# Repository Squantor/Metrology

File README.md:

# General Metrology related projects/tools
This repository contains metrology related hardware/software/mechcanical parts. Stuff like tools, jigs, adapters etc.
## Structure
* [electronics](electronics/README.md) contains all the electronic hardware used in the project.
* [software](software/README.md) contains all the software used in the project. This can be embedded, PC/smartphone or test scripts, anything a computer can execute resides here.
* [mechanical](mechanical/README.md) contains all the CAD drawings, mostly 3d printable objects.
* [documentation](documentation/index.md) contains all project documentation, logs, research, papers, datasheets and more.
## Cloning
This repository makes extensive use of submodules, use ```git clone --recurse-submodules https://github.com/Squantor/Metrology.git``` to clone everything in one go.

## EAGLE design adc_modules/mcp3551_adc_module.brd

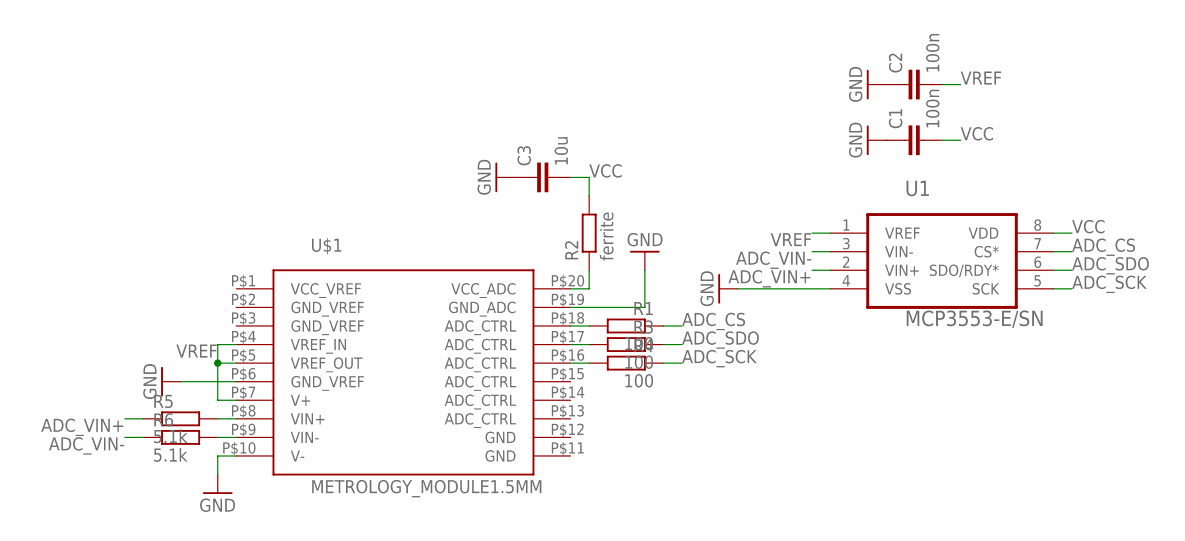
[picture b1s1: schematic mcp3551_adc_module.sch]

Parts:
C1, C2: 100n; C0603
C3: 10u; C0805
R1, R3, R4: 100; R0603
R2: ferrite; R0805
R5, R6: 5.1k; R0805
U1: MCP3553-E/SN; SOIC127P600X175-8N
U$1: METROLOGY_MODULE1.5MM; METROLOGY_MODULE_1.5MM_HOLE

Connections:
ADC_CS: R1.1, U1.7 (CS*)
ADC_SCK: R4.1, U1.5 (SCK)
ADC_SDO: R3.1, U1.6 (SDO/RDY*)
ADC_VIN+: R5.1, U1.2 (VIN+)
ADC_VIN-: R6.1, U1.3 (VIN-)
GND: C1.1, C2.1, C3.1, U1.4 (VSS), U$1.P$6 (GND_VREF), U$1.P$10 (V-), U$1.P$19 (GND_ADC)
unnamed: R2.1, U$1.P$20 (VCC_ADC)
unnamed: R1.2, U$1.P$18 (ADC_CTRL)
unnamed: R3.2, U$1.P$17 (ADC_CTRL)
unnamed: R4.2, U$1.P$16 (ADC_CTRL)
unnamed: R5.2, U$1.P$8 (VIN+)
unnamed: R6.2, U$1.P$9 (VIN-)
VCC: C1.2, C3.2, R2.2, U1.8 (VDD)
VREF: C2.2, U1.1 (VREF), U$1.P$4 (VREF_IN), U$1.P$5 (VREF_OUT), U$1.P$7 (V+)

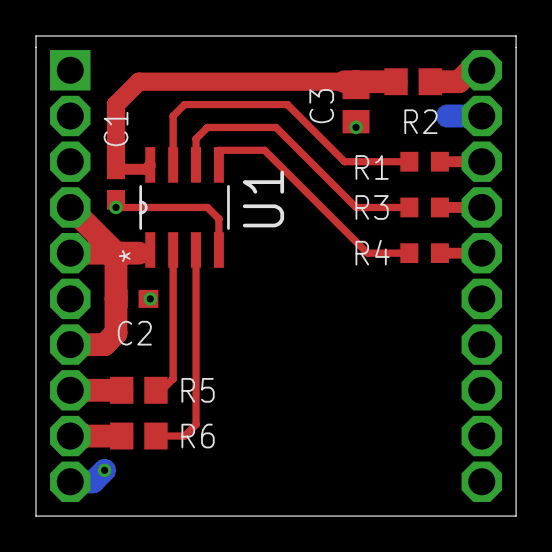
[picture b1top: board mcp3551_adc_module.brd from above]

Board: 2 copper layers, 26.7 x 26.7 mm, 11 parts (0 on the bottom side), 14 nets.

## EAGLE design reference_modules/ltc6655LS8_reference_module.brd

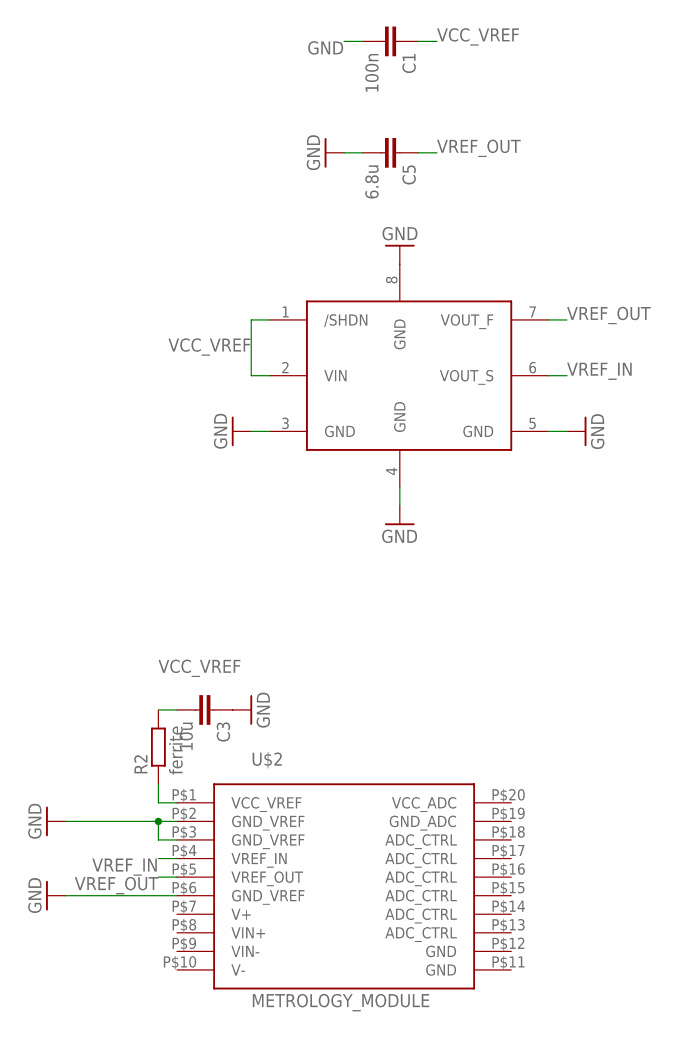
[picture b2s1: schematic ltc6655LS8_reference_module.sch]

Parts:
C1: 100n; C0603
C3: 10u; C0805
C5: 6.8u; C050-075X075
R2: ferrite; R0805
U$1: LTC6655LS8_ELONG; LS8_ELONG
U$2: METROLOGY_MODULE

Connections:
GND: C1.2, C3.1, C5.2, U$1.3 (GND), U$1.4 (GND), U$1.5 (GND), U$1.8 (GND), U$2.P$2 (GND_VREF), U$2.P$3 (GND_VREF), U$2.P$6 (GND_VREF)
unnamed: R2.1, U$2.P$1 (VCC_VREF)
VCC_VREF: C1.1, C3.2, R2.2, U$1.1 (/SHDN), U$1.2 (VIN)
VREF_IN: U$1.6 (VOUT_S), U$2.P$4 (VREF_IN)
VREF_OUT: C5.1, U$1.7 (VOUT_F), U$2.P$5 (VREF_OUT)

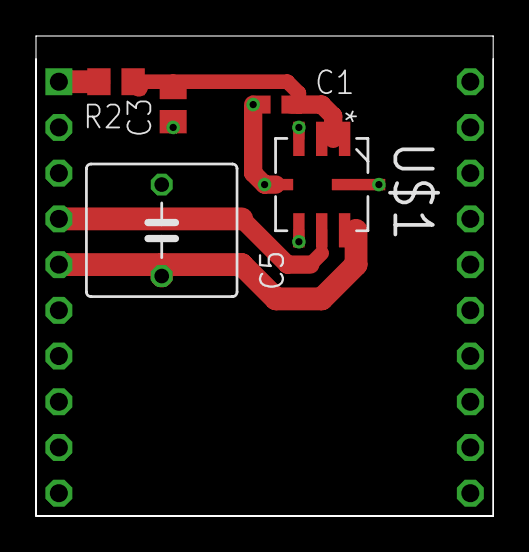
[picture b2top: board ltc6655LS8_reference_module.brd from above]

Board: 2 copper layers, 25.4 x 26.7 mm, 6 parts (0 on the bottom side), 5 nets.

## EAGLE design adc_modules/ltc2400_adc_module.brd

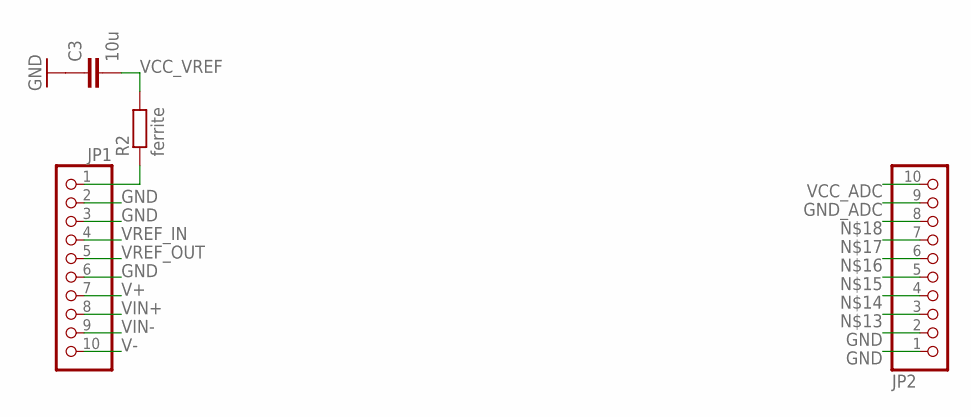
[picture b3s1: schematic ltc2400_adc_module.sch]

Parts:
C3: 10u; C0805
JP1, JP2: PINHD-1X10NORM_OCT; 1X10_NORMAL_OCT
R2: ferrite; R0805

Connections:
GND: C3.1, JP1.2, JP1.3, JP1.6, JP2.1, JP2.2
GND_ADC: JP2.9
unnamed: JP1.1, R2.1
V+: JP1.7
V-: JP1.10
VCC_ADC: JP2.10
VCC_VREF: C3.2, R2.2
VIN+: JP1.8
VIN-: JP1.9
VREF_IN: JP1.4
VREF_OUT: JP1.5

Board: 2 copper layers, 4 parts (0 on the bottom side), 3 nets, no tracks yet.

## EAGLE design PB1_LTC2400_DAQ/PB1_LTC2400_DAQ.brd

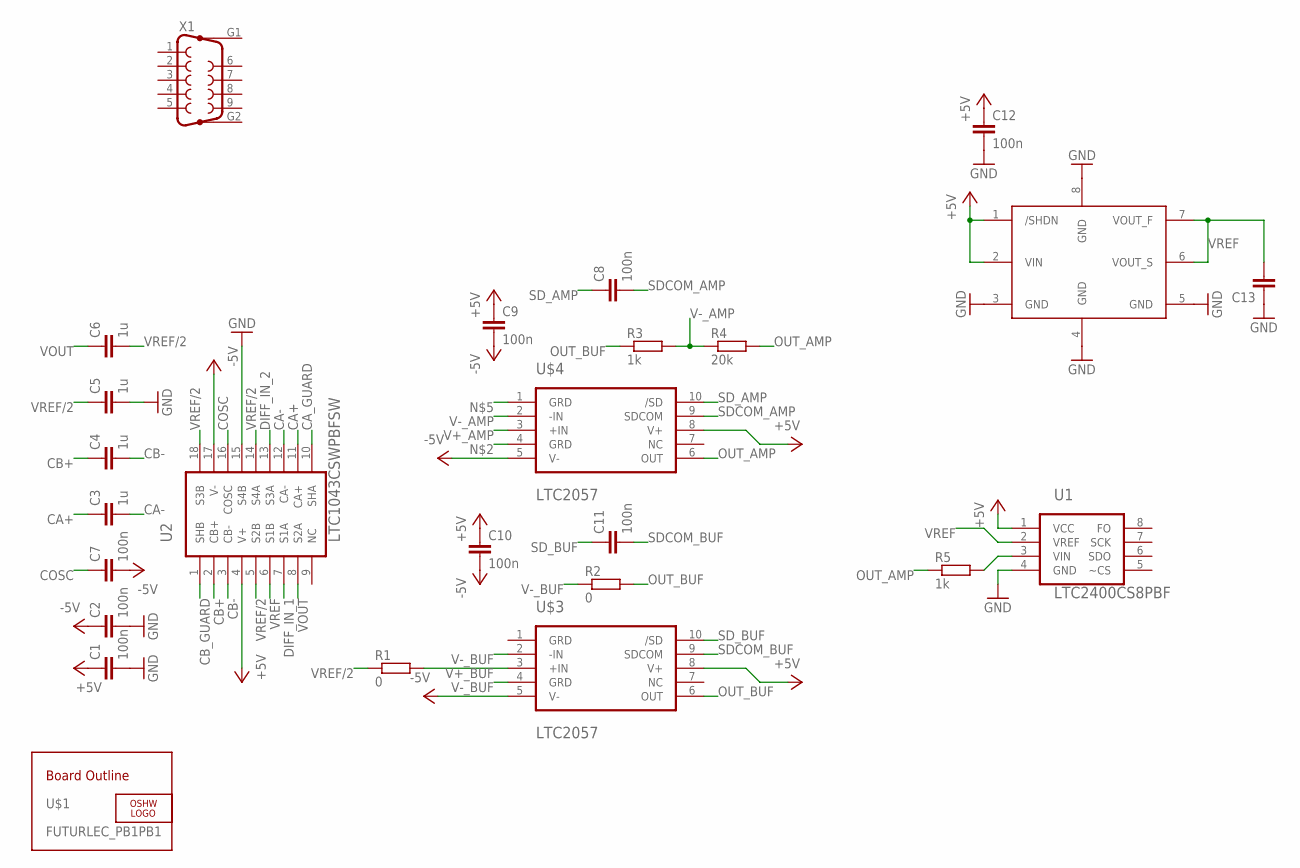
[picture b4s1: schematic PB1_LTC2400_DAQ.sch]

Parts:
C1, C2, C7, C9, C10, C12: 100n; C1812K
C3, C4, C5, C6: 1u; C2220K
C8, C11: 100n; C0603
C13: C-EU075-063X106; C075-063X106
LOGO1: OSHW_LOGO_8MILX0200-NT; OSHW_8X200_NOTEXT
R1, R2: 0; R0805
R3, R5: 1k; R0805
R4: 20k; R0805
U1: LTC2400CS8PBF; SOIC127P600X175-8N
U2: LTC1043CSWPBFSW; SOIC127P1032X264-18N
U$1: FUTURLEC_PB1PB1; FUTURLEC_PB1
U$2: LTC6655LS8_ELONG; LS8_ELONG
U$3, U$4: LTC2057; MS-MSOP10
X1: F09VP

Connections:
+5V: C1.1, C9.1, C10.1, C12.1, U1.1 (VCC), U2.4 (V+), U$2.1 (/SHDN), U$2.2 (VIN), U$3.8 (V+), U$4.8 (V+)
-5V: C2.1, C7.2, C9.2, C10.2, U2.17 (V-), U$3.5 (V-), U$4.5 (V-)
CA+: C3.1, U2.11 (CA+)
CA-: C3.2, U2.12 (CA-)
CA_GUARD: U2.10 (SHA)
CB+: C4.1, U2.2 (CB+)
CB-: C4.2, U2.3 (CB-)
CB_GUARD: U2.1 (SHB)
COSC: C7.1, U2.16 (COSC)
DIFF_IN_1: U2.7 (S1A)
DIFF_IN_2: U2.13 (S3A)
GND: C1.2, C2.2, C5.2, C12.2, C13.1, U1.4 (GND), U2.15 (S4B), U$2.3 (GND), U$2.4 (GND), U$2.5 (GND), U$2.8 (GND)
unnamed: R5.2, U1.3 (VIN)
OUT_AMP: R4.2, R5.1, U$4.6 (OUT)
OUT_BUF: R2.2, R3.1, U$3.6 (OUT)
SDCOM_AMP: C8.2, U$4.9 (SDCOM)
SDCOM_BUF: C11.2, U$3.9 (SDCOM)
SD_AMP: C8.1, U$4.10 (/SD)
SD_BUF: C11.1, U$3.10 (/SD)
V+_AMP: U$4.3 (+IN)
V+_BUF: R1.2, U$3.3 (+IN)
V-_AMP: R3.2, R4.1, U$4.2 (-IN)
V-_BUF: R2.1, U$3.2 (-IN), U$3.4 (GRD)
VOUT: C6.1, U2.8 (S2A)
VREF: C13.2, U1.2 (VREF), U2.6 (S1B), U$2.6 (VOUT_S), U$2.7 (VOUT_F)
VREF/2: C5.1, C6.2, R1.1, U2.5 (S2B), U2.14 (S4A), U2.18 (S3B)

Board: 2 copper layers, 26 parts (2 on the bottom side), 21 nets, no tracks yet.

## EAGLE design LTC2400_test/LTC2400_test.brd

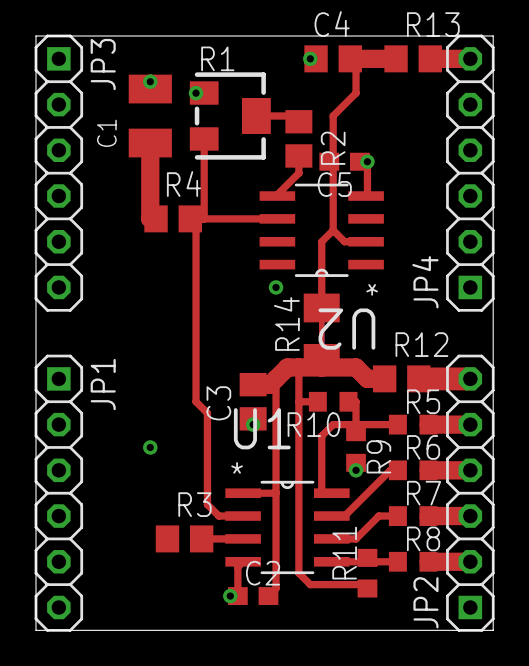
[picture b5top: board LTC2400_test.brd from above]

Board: 2 copper layers, 25.4 x 33.0 mm, 26 parts (1 on the bottom side), 17 nets.

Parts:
C1: SMC_B
C2, C5: 100n; C0603
C3, C4: 10u; C0805
JP1, JP2, JP3, JP4: 1X06_SMALL
R1: 100k; RTRIM3214W
R2: 4.7M; R0805
R3: 5.1k; R0805
R4: 2.2; R0805
R5, R6, R7, R8: 100; R0603
R9: 60Hz; R0603
R10: 50Hz; R0603
R11: 10k; R0603
R12, R13: ferrite; R0805
R14, R15: M1206
U1: LTC2400CS8PBF; SOIC127P600X175-8N@1
U2: LT1019A-2.5PBFS8; SOIC127P600X175-8N

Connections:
+5V: C2.2, C3.2, C4.2, C5.2, R10.2, R11.1, R12.1, R13.1, R14.1, R14.2, U1.1, U2.2
CS: R8.1, R11.2, U1.5
FO: R5.1, R9.1, R10.1, U1.8
GND: C1.-, C2.1, C3.1, C4.1, C5.1, JP1.2, JP1.4, JP1.6, JP2.1, JP3.6, JP4.1, R1.1, R9.2, R15.1, R15.2, U1.4, U2.4
unnamed: JP4.6, R13.2
unnamed: JP2.6, R12.2
unnamed: C1.+, R4.1
unnamed: R3.2, U1.3
unnamed: R1.2, R2.1
unnamed: JP2.2, R8.2
unnamed: JP2.3, R7.2
unnamed: JP2.4, R6.2
unnamed: JP2.5, R5.2
SCK: R6.1, U1.7
SDO: R7.1, U1.6
TRIM: R2.2, U2.5
VREF: R1.3, R4.2, U1.2, U2.6

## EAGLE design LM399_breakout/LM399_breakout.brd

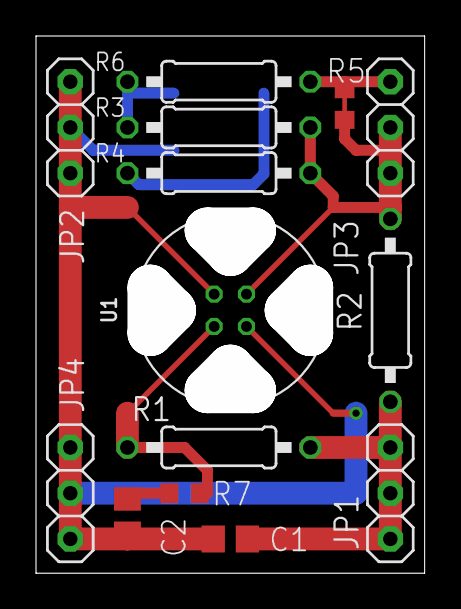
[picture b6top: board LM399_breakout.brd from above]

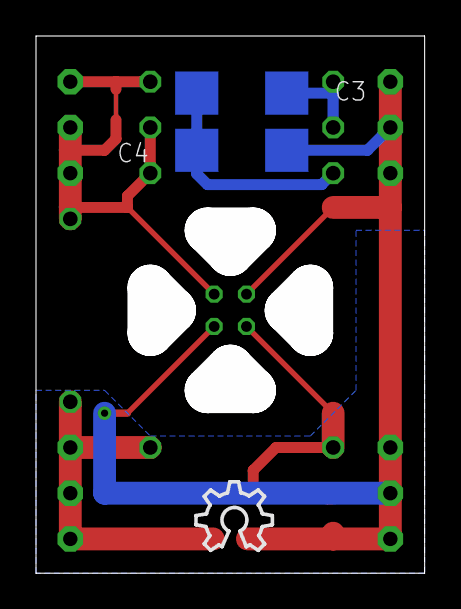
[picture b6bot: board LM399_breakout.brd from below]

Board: 2 copper layers, 21.6 x 29.8 mm, 17 parts (3 on the bottom side), 7 nets.

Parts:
C1: 1u; C0805
C2: 10u; C0805
C3, C4: SMC_C
JP1: VCC; 1X03_SMALL
JP2, JP4: GND; 1X03_SMALL
JP3: Zener; 1X03_SMALL
R1: inrush; 0207/10
R2: 220k; 0207/10
R3, R4, R6: 0207/10
R5: WIRE0603; R0603/BRIDGE
R7: R0603
U1: LM399; H4-TO46-4PIN
U$1: OSHW_8X150_NOTEXT

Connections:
+15V: C1.1, JP1.1, JP1.2, JP1.3, R1.2, R2.2
GND: C1.2, C2.2, C4.-, JP2.1, JP2.2, JP2.3, JP4.1, JP4.2, JP4.3, U1.2, U1.4
unnamed: R1.1, R7.1, U1.3
unnamed: C2.1, R7.2
unnamed: C3.-, C4.+, R4.2
unnamed: C3.+, R3.2, R6.1
ZENER: JP3.1, JP3.2, JP3.3, R2.1, R3.1, R4.1, R5.1, R5.2, R6.2, U1.1

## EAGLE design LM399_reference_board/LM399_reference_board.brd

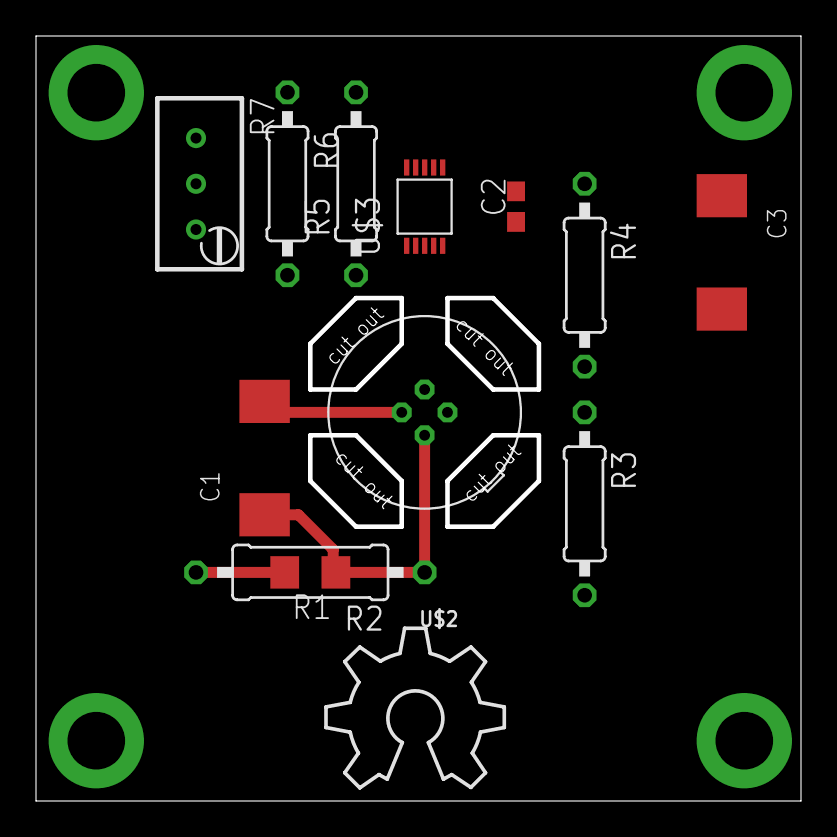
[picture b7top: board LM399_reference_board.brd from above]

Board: 2 copper layers, 42.5 x 42.5 mm, 13 parts (0 on the bottom side), 7 nets.

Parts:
C1, C3: 10u; SMC_D
C2: 100n; C0603
R1: inrush; R1206
R2: inrush; 0309/12
R3: 220k; 0207/10
R4: 5k; 0207/10
R5: 8.8k; 0207/10
R6: 19k; 0207/10
R7: RTRIMT93YA
U$1: OSHW_8X350_NOTEXT
U$2: LM399; H4-TO46-4PIN
U$3: LTC2057; MS-MSOP10

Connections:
+15V: C2.2, C3.+, R1.2, R2.2, R3.2, U$3.8
GND: C1.-, C2.1, C3.-, R7.2, R7.3, U$2.2, U$2.3, U$3.5
unnamed: C1.+, R1.1, R2.1, U$2.4
unnamed: R5.1, R6.2, U$3.1, U$3.2, U$3.4
unnamed: R4.1, R5.2, U$3.6
unnamed: R6.1, R7.1
VZENER: R3.1, R4.2, U$2.1, U$3.3

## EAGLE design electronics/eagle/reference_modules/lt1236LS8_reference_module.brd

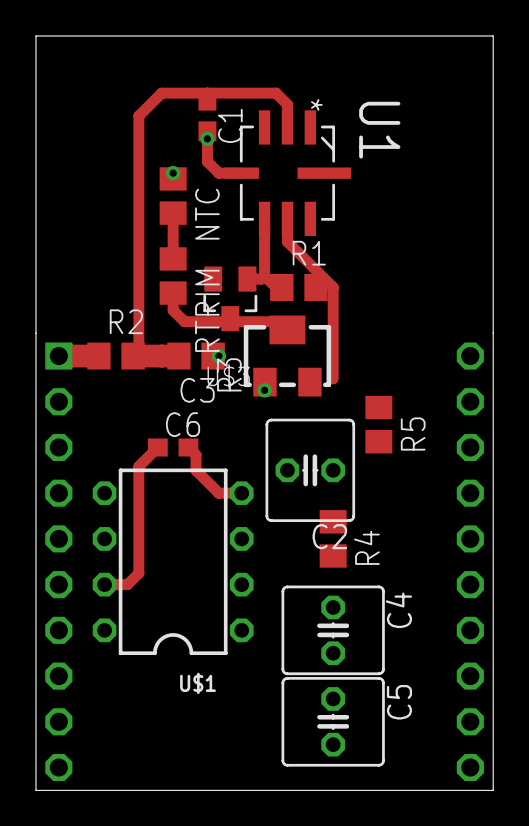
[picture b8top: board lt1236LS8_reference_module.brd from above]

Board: 2 copper layers, 25.4 x 41.9 mm, 17 parts (0 on the bottom side), 12 nets.

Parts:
C1, C6: 100n; C0603
C2, C4, C5: 1u; C025-060X050
C3: 10u; C0805
NTC: R0805
R1: 27k; R0805
R2: ferrite; R0805
R3: 50k; RTRIM3224W
R4, R5: 36k; R0805
RTRIM: R0805
U1: LT1236BILS8-5PBFLS8_ELONG; LS8_ELONG
U$1: LT1001; N8-PDIP8
U$2: METROLOGY_MODULE
U$3: BAS17; SOT23_HAND

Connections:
GND: C1.2, C3.1, C5.2, C6.2, NTC.1, R3.1, U1.4, U$1.4, U$2.P$2, U$2.P$3, U$2.P$6
unnamed: R2.1, U$2.P$1
unnamed: R3.2, RTRIM.2, U$3.3
unnamed: NTC.2, RTRIM.1
unnamed: C2.1, R4.1, R5.2
unnamed: C4.1, R4.2, U$1.3
unnamed: C4.2, C5.1
VCC_VREF: C1.1, C3.2, C6.1, R2.2, U1.2, U$1.7
VREF_IN: C2.2, U$1.2, U$2.P$4
VREF_OUT: U$1.6, U$2.P$5
VREF_OUT_UNFILT: R1.2, R3.3, R5.1, U1.6
VREF_TRIM: R1.1, U1.5, U$3.1

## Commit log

2015-03-19 * Added Geller SVR board outline clone with plated through holes. This is to make future references compatible with this form factor.
2015-03-19 * Started with the LTC6655 reference board, same form factor as the geller voltage reference
2015-03-19 * start of the LM399 board, copied the Geller board dimensions
2015-03-19 * added start of the lm399 reference
2015-03-23 * Additional work with LM399
2015-03-26 * finished LM399 breakout with a optional filter stage
2015-03-26 * Final touchups on LM399 breakout board, ready to order!
2015-04-09 * added hp34401a control application
2015-04-09 * added first modules
2015-04-16 * fixed mistakes with the lm399 board
2016-02-10 * added fluke845 references board project
2016-02-10 * layed out fluke845 reference board
2016-02-10 * small fixes on the PCB
2016-02-10 * added PB1 powersupply project * added LT1021 project (preparation for LT1236LS8 tester)
2016-02-20 * started on the PB1 powersupply
2016-02-21 * started with LTC2400 test board, but... its better to just begin with a PB1 sized board * started with PB1 board with LTC2400 etc
2016-02-21 * updated PB1 board, need a lot more lessons learned with it, so lets leave it for now * updated LTC2400 test board, going to focus on that first
2016-02-22 * added a bunch of reference modules, starting with LTC6655's
2016-02-22 * added ADC modules, first up the MCP3551 ADC
2016-02-23 * finished ltc6655 reference board
2016-02-23 * small modifications on ltc2400_adc_module
2016-02-23 * removed old unused project * switched to module outline layout, this way i am sure the boards will remain the same
2016-02-23 * updated and almost finished MCP3551 ADC module
2016-02-24 * updated board format * made the LTC6655 reference module more compact, hopefully better * small modifications to the MCP355X ADC module
2016-03-02 * modified boards and processed for production
2016-03-07 * populating initial project
2016-03-07 * cleaned up files from old project
2016-03-13 * Made functional MCP355X driver thingy
2016-03-13 * project file update
2016-03-14 * readout of MCP3550, some strange things are happening... Need electrical tests
2016-03-18 * some extra statistics added * fixed calculation from LSB to volt, loss of precision
2016-03-24 * small updates to voltmeter, adapted to optoisolation
2016-12-10 * moved all the PCB projects made in eagle to their own dir
2016-12-10 * created a MCP355X breakout module
2016-12-10 * added LTC6655 breakout module
2016-12-10 * created module for REF50XX series references
2016-12-10 * started with the MCP355X module fillout
2016-12-10 * finished routing MCP355X PCB
2016-12-10 * added OHSW logo and version
2016-12-10 * small mods and optimizations
2016-12-10 * again some small modifications
2016-12-10 * added LTC2400 module
2016-12-11 * project updates
2016-12-13 * changed input filter caps from 0603 to 0805
2016-12-19 * small mods
2016-12-20 * added REF schematic stuff
2016-12-21 * placed components on PCB and started positioning
2016-12-21 * more PCB layout stuff
2016-12-22 * added terminator module
2016-12-22 * added attenuator module
2016-12-22 * added partially routed pcb for the terminator
2016-12-27 * Some more layouting of the REF50XX module
2017-01-07 * changed bad footprints for the WIMA MKS-02 1uF caps
2017-01-07 * changes a mistake on layouting on wrong grid
2017-01-07 * added git ignore
2017-01-07 * updated the LTC6655 reference board
2017-01-07 * more ignores
2017-01-07 * some small modifications
2017-01-07 * redid partially REF5040 reference board
2017-11-10 * added a few dirs for the babims project * touched a few README.md's
2017-11-10 * added kicad projects
2017-11-10 * different naming scheme
2017-11-10 * added 3 babims expansion card * added 1 babims motherboard
2017-11-10 * added some explanation of the BABIMS project
2017-11-10 * project updates for prototyping card
2017-11-11 * started on the babims prototyping board
2017-11-13 * added hp 15 pin card extender project
2017-11-13 * modified .gitignore * added all the missing -cache.lib files * updated the hp card extender 15 pins
2017-11-27 * added new 96 pin backplane for babims
2017-11-27 * first definition of the connection nets
2018-12-15 reorganisation of the metrology collection library
2018-12-15 add private pcb component library
2018-12-15 added Readme with checkout instructions
2018-12-15 updated root readme with additional instructions
2018-12-15 added initial project for the endpoint unit of the flatcable jig system
2018-12-15 updated schematic with a few parts
2018-12-15 updated library
2018-12-15 started layout, still need to add the endpad connections
2018-12-16 single quotes are not backticks ;-)
2018-12-16 updated library with newer coaxial connections
2018-12-16 layout completed, now silk screen
2018-12-16 updated silkscreen position
2018-12-16 added box image
2018-12-16 updated versionnumber, adjusted cutout line thickness to 0.1mm
2018-12-17 added cache library
2018-12-17 added jumperable grounds
2019-01-21 updated pcb library
2019-01-21 updated versionnumbers, no real changes actually
2019-08-09 moved extender card project
2019-08-09 updated submodule
2019-08-09 added wheatstone bridge+hamon divider project
2019-08-09 updated gitignore
2019-08-09 added mounting holes and case net
2019-08-09 added initial Wheatstone bridge and Hamon divider
2019-08-10 added LT1021 reference project start, already added reference and trim schematic
2019-11-05 updated to newer PCB library
2019-11-05 added bypass capacitor tester project
2019-11-05 completed schematic
2019-11-05 fixed all ERC errors
2019-11-05 started layout
2019-11-10 newer PCB library
2019-11-10 removed defunct footprint library
2019-11-10 changed coaxial connectors to SMA edge connectors
2019-11-10 further placement
2019-11-12 changed power connector to something I use often
2019-11-12 changed dut footprint, placement completed
2019-11-12 silk placement completed
2019-11-12 updated versionnumber
2022-09-23 moving around files
2022-09-23 harmonized with generic project library
2022-09-25 started with dslogic logic analyzer breakout board
2022-09-25 completed schematic, board layout and updated readme
2022-09-26 added some coplanar waveguides
2022-09-30 start with 4 pin logic analyzer probe
2022-09-30 edge footprints for probes
2022-09-30 added labels
2022-09-30 made unplaceable labels invisible
2022-09-30 updated pinout
2022-10-03 copied over 4 channel logic probe to 8
2022-10-03 updated to 8 channels
2022-10-03 WIP routing and placing
2022-10-04 WIP 8 channel dslogic probe
2022-10-07 fixing connector DRC issues
2022-10-07 fixed DRC issues with connectors
2022-10-07 added breakout for broadcom SiPM
2022-10-07 WIP schematic entry
2022-10-07 Started initial layout for breakout
2022-10-09 updated versionnumber and reviewed
2022-10-09 reviewd 4 bit logic probe circuit
2022-10-09 reviewed PCB and updated versionnumber
2023-04-14 minor changes
2023-04-14 started with notch filter project
2023-04-15 further layout and placing
2023-04-15 added filter and attenuator to schematic and placed components
2023-04-19 changed resistor networks to be more flexible, placed some components
2023-04-19 added compensation capacitor, placed and routed filter
2023-04-20 footprint changes, changed power rails, silk placed, added labels, increased size of labels
2023-04-21 added 1M input resistor
2023-04-21 started with oscillator prototyping board
2023-04-21 layout completed on prototype oscillator prototype
2023-04-23 updated resistor values and some minor routing updates
2023-04-28 fixed errors with proto oscillator
2023-04-28 added additional adjust resistor and updated values
2023-04-28 started with PCB layout of single dual opamp with standard gain control
2023-04-28 placing and routing in progress, changed some ordering of resistors
2023-04-28 updated parts
2023-04-28 placing and routing further
2023-04-30 updated some shielded components, changing routing of some nets keeping the ground plane as much contigious as possible
2023-04-30 place and route and silk placement completed
2023-05-01 small modification made to select output point
2023-05-01 started variant 2 of high purity oscillator
2023-05-01 added oscillator variant with dual single opamp
2023-05-01 completed place and routing
2023-05-01 updated footprints
2023-05-07 ERC/DRC passes, small ergonomic changes
2023-05-07 reviewed
2023-05-07 review completed
2023-05-07 small changes in output pin
2023-05-30 updated notch filter
2023-05-31 fixed aisler warnings/errors
2023-07-01 conversion to kicad 7
2023-07-17 removed labels and minor optimisations
2023-07-17 copied notch filter to a SMT version
2024-03-29 started with linear technology style wien bridge oscillator
2024-04-03 added vactrol housing files
2024-05-03 added passive filter project
2024-05-03 updated with kicad 7 ignores
2024-05-03 completed passive filter
